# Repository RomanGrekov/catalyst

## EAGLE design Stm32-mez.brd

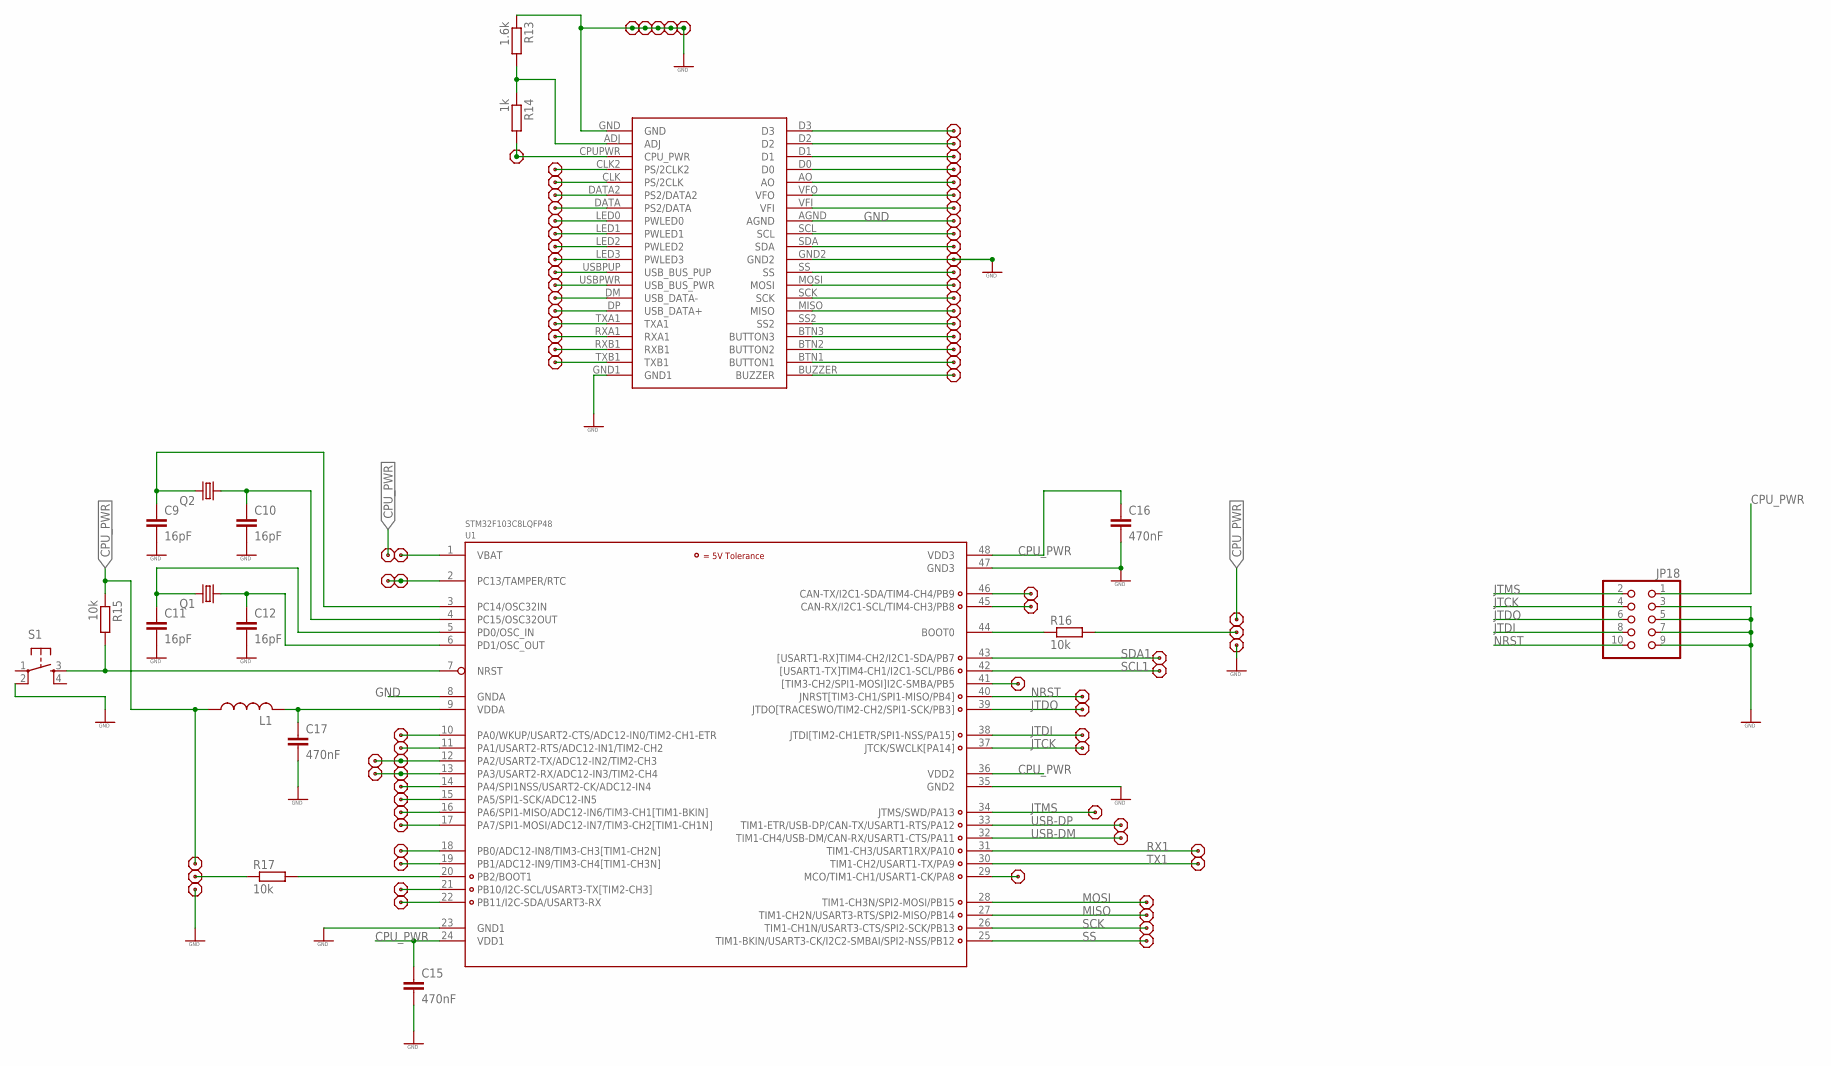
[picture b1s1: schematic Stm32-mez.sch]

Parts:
C9, C10, C11, C12: 16pF; C1206
C15, C16, C17: 470nF; C1206
JP5, JP6, JP7, JP8, JP10, JP11, JP12, JP13, JP14, JP15, JP16, JP17, JP19, JP20, JP21, JP22, JP23, JP24, JP25, JP26, JP27, JP28, JP29, JP30, JP31, JP32, JP33, JP34, JP35, JP36, JP37, JP38, JP39, JP40, JP41, JP42, JP43, JP44, JP45, JP46, JP47, JP48, JP49, JP50, JP51, JP52, JP53, JP54, JP55, JP56, JP57, JP58, JP59, JP60, JP61, JP62, JP63, JP64, JP65, JP66, JP67, JP68, JP69, JP70, JP71, JP72, JP73, JP74, JP75, JP76, JP77, JP78, JP79, JP80, JP81, JP82, JP83, JP84, JP85, JP86, JP87, JP88, JP89, JP90, JP91: PINHD-1X1PIN; 1X01
JP18: PINHD-2X5; 2X05
L1: L-US0207/15; 0207/15
Q1: CRYSTALHC49U-V; HC49U-V
Q2: CRYSTALTC26H; TC26H
R13: 1.6k; R1206
R14: 1k; R1206
R15, R16, R17: 10k; R1206
S1: TAC_SWITCHPTH; TACTILE-PTH
U1: STM32F103C8LQFP48; LQFP48
U$2: CPU_CON; CPU_SHIELD

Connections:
CPU_PWR: C15.1, C16.1, JP5.1, JP16.1, JP18.1, JP24.1, JP54.1, L1.1, R14.2, R15.1, U1.24 (VDD1), U1.36 (VDD2), U1.48 (VDD3), U$2.CPUPWR (CPU_PWR)
GND: C9.2, C10.2, C11.2, C12.2, C15.2, C16.2, C17.2, JP10.1, JP11.1, JP12.1, JP13.1, JP14.1, JP18.3, JP18.5, JP18.7, JP18.9, JP25.1, JP55.1, JP90.1, JP91.1, R13.1, S1.2, U1.8 (GNDA), U1.23 (GND1), U1.35 (GND2), U1.47 (GND3), U$2.AGND, U$2.GND, U$2.GND1, U$2.GND2
JTCK: JP18.4, JP22.1, U1.37 (JTCK/SWCLK[PA14])
JTDI: JP18.8, JP21.1, U1.38 (JTDI[TIM2-CH1ETR/SPI1-NSS/PA15])
JTDO: JP18.6, JP20.1, U1.39 (JTDO[TRACESWO/TIM2-CH2/SPI1-SCK/PB3])
JTMS: JP18.2, JP26.1, U1.34 (JTMS/SWD/PA13)
MISO: JP32.1, U1.27 (TIM1-CH2N/USART3-RTS/SPI2-MISO/PB14)
MOSI: JP31.1, U1.28 (TIM1-CH3N/SPI2-MOSI/PB15)
unnamed: R15.2, S1.3, U1.7 (NRST)
unnamed: R13.2, R14.1, U$2.ADJ
unnamed: C12.1, Q1.1, U1.6 (PD1/OSC_OUT)
unnamed: C11.1, Q1.2, U1.5 (PD0/OSC_IN)
unnamed: C10.1, Q2.1, U1.4 (PC15/OSC32OUT)
unnamed: C9.1, Q2.2, U1.3 (PC14/OSC32IN)
unnamed: JP8.1, JP17.1, U1.2 (PC13/TAMPER/RTC)
unnamed: R16.1, U1.44 (BOOT0)
unnamed: JP23.1, R16.2
unnamed: JP38.1, U1.46 (CAN-TX/I2C1-SDA/TIM4-CH4/PB9)
unnamed: JP37.1, U1.45 (CAN-RX/I2C1-SCL/TIM4-CH3/PB8)
unnamed: JP39.1, U1.41 ([TIM3-CH2/SPI1-MOSI]I2C-SMBA/PB5)
unnamed: JP40.1, U1.29 (MCO/TIM1-CH1/USART1-CK/PA8)
unnamed: JP41.1, U1.10 (PA0/WKUP/USART2-CTS/ADC12-IN0/TIM2-CH1-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)
unnamed: JP43.1, U1.11 (PA1/USART2-RTS/ADC12-IN1/TIM2-CH2)
unnamed: JP6.1, JP42.1, U1.12 (PA2/USART2-TX/ADC12-IN2/TIM2-CH3)
unnamed: JP7.1, JP44.1, U1.13 (PA3/USART2-RX/ADC12-IN3/TIM2-CH4)
unnamed: JP45.1, U1.14 (PA4/SPI1NSS/USART2-CK/ADC12-IN4)
unnamed: JP46.1, U1.15 (PA5/SPI1-SCK/ADC12-IN5)
unnamed: JP47.1, U1.16 (PA6/SPI1-MISO/ADC12-IN6/TIM3-CH1[TIM1-B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)
unnamed: JP48.1, U1.17 (PA7/SPI1-MOSI/ADC12-IN7/TIM3-CH2[TIM1-C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)
unnamed: JP49.1, U1.18 (PB0/ADC12-IN8/TIM3-CH3[TIM1-CH2N])
unnamed: JP50.1, U1.19 (PB1/ADC12-IN9/TIM3-CH4[TIM1-CH3N])
unnamed: R17.2, U1.20 (PB2/BOOT1)
unnamed: JP52.1, U1.21 (PB10/I2C-SCL/USART3-TX[TIM2-CH3])
unnamed: JP53.1, U1.22 (PB11/I2C-SDA/USART3-RX)
unnamed: JP51.1, R17.1
unnamed: JP73.1, U$2.D3
unnamed: JP72.1, U$2.D2
unnamed: JP71.1, U$2.D1
unnamed: JP70.1, U$2.D0
unnamed: JP69.1, U$2.AO
unnamed: JP68.1, U$2.VFO
unnamed: JP67.1, U$2.VFI
unnamed: JP66.1, U$2.SCL
unnamed: JP65.1, U$2.SDA
unnamed: JP64.1, U$2.SS
unnamed: JP63.1, U$2.MOSI
unnamed: JP62.1, U$2.SCK
unnamed: JP61.1, U$2.MISO
unnamed: JP60.1, U$2.SS2
unnamed: JP59.1, U$2.BTN3 (BUTTON3)
unnamed: JP58.1, U$2.BTN2 (BUTTON2)
unnamed: JP57.1, U$2.BTN1 (BUTTON1)
unnamed: JP56.1, U$2.BUZZER
unnamed: JP74.1, U$2.TXB1
unnamed: JP75.1, U$2.RXB1
unnamed: JP76.1, U$2.RXA1
unnamed: JP77.1, U$2.TXA1
unnamed: JP78.1, U$2.DP (USB_DATA+)
unnamed: JP79.1, U$2.DM (USB_DATA-)
unnamed: JP80.1, U$2.USBPWR (USB_BUS_PWR)
unnamed: JP81.1, U$2.USBPUP (USB_BUS_PUP)
unnamed: JP82.1, U$2.LED3 (PWLED3)
unnamed: JP83.1, U$2.LED2 (PWLED2)
unnamed: JP84.1, U$2.LED1 (PWLED1)
unnamed: JP85.1, U$2.LED0 (PWLED0)
unnamed: JP86.1, U$2.DATA (PS2/DATA)
unnamed: JP87.1, U$2.DATA2 (PS2/DATA2)
unnamed: JP88.1, U$2.CLK (PS/2CLK)
unnamed: JP89.1, U$2.CLK2 (PS/2CLK2)
NRST: JP18.10, JP19.1, U1.40 (JNRST[TIM3-CH1/SPI1-MISO/PB4])
RX1: JP27.1, U1.31 (TIM1-CH3/USART1RX/PA10)
SCK: JP33.1, U1.26 (TIM1-CH1N/USART3-CTS/SPI2-SCK/PB13)
SCL1: JP36.1, U1.42 ([USART1-TX]TIM4-CH1/I2C1-SCL/PB6)
SDA1: JP35.1, U1.43 ([USART1-RX]TIM4-CH2/I2C1-SDA/PB7)
SS: JP34.1, U1.25 (TIM1-BKIN/USART3-CK/I2C2-SMBAI/SPI2-NSS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)
TX1: JP28.1, U1.30 (TIM1-CH2/USART1-TX/PA9)
USB-DM: JP29.1, U1.32 (TIM1-CH4/USB-DM/CAN-RX/USART1-CTS/PA11)
USB-DP: JP30.1, U1.33 (TIM1-ETR/USB-DP/CAN-TX/USART1-RTS/PA12)
VBAT: JP15.1, U1.1 (VBAT)
VDDA: C17.1, L1.2, U1.9 (VDDA)

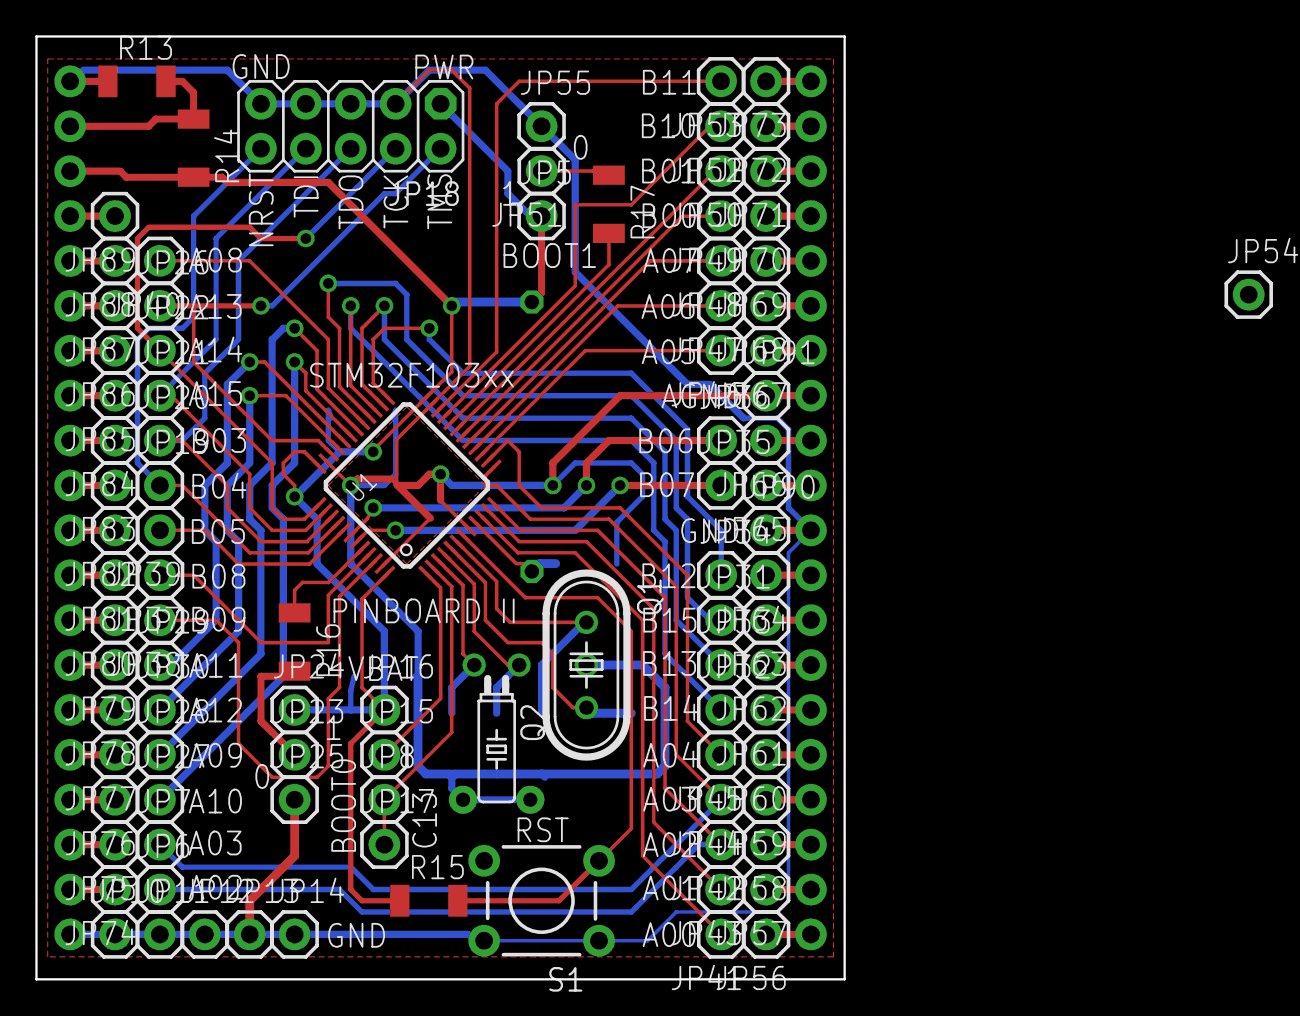
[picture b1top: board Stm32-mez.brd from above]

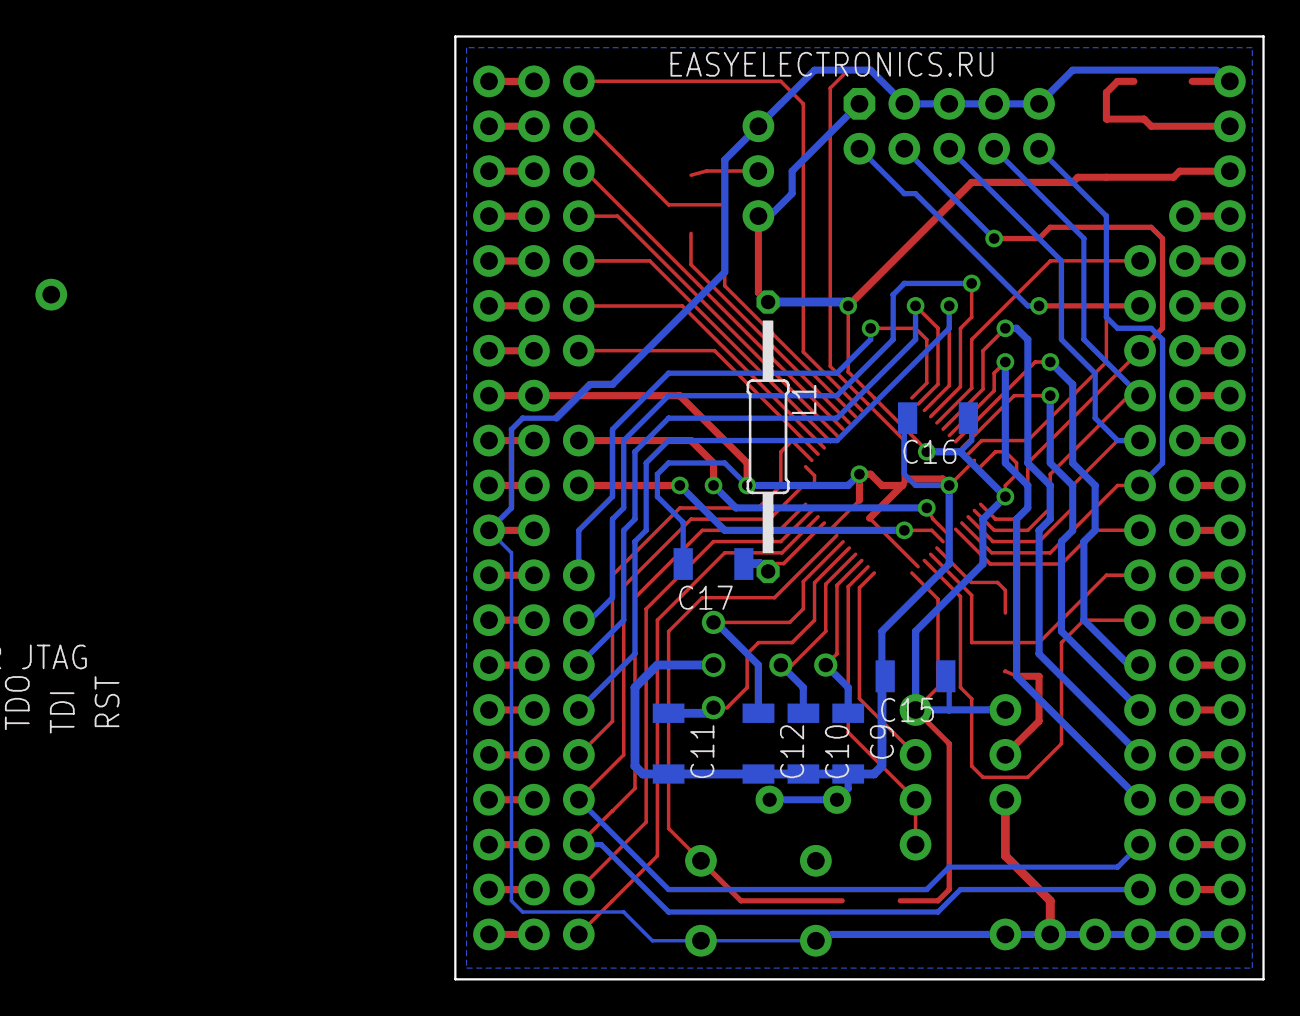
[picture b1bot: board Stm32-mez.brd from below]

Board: 2 copper layers, 45.7 x 53.3 mm, 104 parts (8 on the bottom side), 80 nets.

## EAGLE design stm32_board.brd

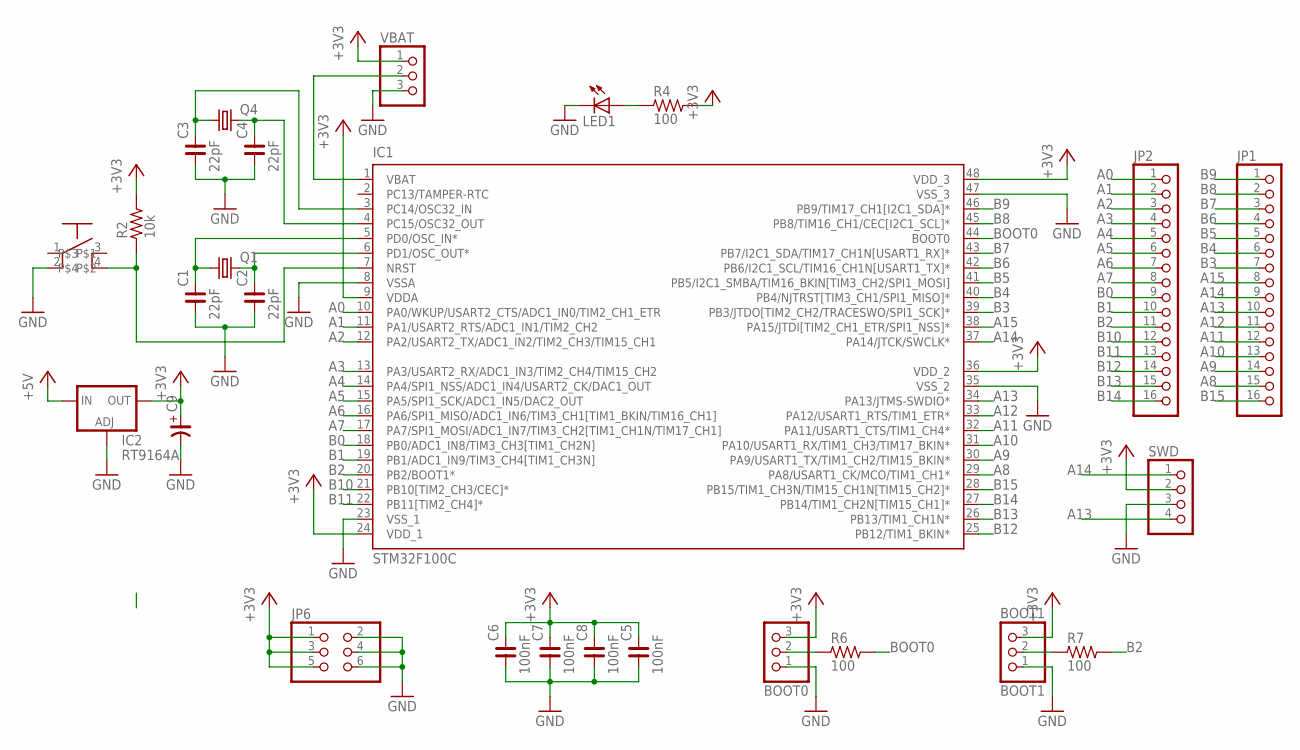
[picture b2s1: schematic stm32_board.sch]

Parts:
BOOT0: PINHD-1X3; 1X03
BOOT1: BOOT1; 1X03
C1, C2, C3, C4: 22pF; C1206
C5, C6, C7, C8: 100nF; C1206
C9: CP_SV-D; CSV-D
IC1: STM32F100C; LQFP48
IC2: RT9164A; DPACK
JP1, JP2: PINHD-1X16; 1X16
JP6: PINHD-2X3; 2X03
LED1: LEDCHIPLED_0805; CHIPLED_0805
Q1: CRYSTALHC49U-V; HC49U-V
Q4: CRYSTALTC26V; TC26V
R2: 10k; R1206
R4, R6, R7: 100; R1206
S1: BUTTON
SWD: PINHD-1X4; 1X04
VBAT: PINHD-1X3; 1X03

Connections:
+3V3: BOOT0.3, BOOT1.3, C5.2, C6.2, C7.2, C8.2, C9.+, IC1.9 (VDDA), IC1.24 (VDD_1), IC1.36 (VDD_2), IC1.48 (VDD_3), IC2.4 (OUT), JP6.1, JP6.3, JP6.5, R2.2, R4.2, SWD.2, VBAT.1
+5V: IC2.3 (IN)
A0: IC1.10 (PA0/WKUP/USART2_CTS/ADC1_IN0/TIM2_CH1_E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), JP2.1
A1: IC1.11 (PA1/USART2_RTS/ADC1_IN1/TIM2_CH2), JP2.2
A2: IC1.12 (PA2/USART2_TX/ADC1_IN2/TIM2_CH3/TIM15_C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), JP2.3
A3: IC1.13 (PA3/USART2_RX/ADC1_IN3/TIM2_CH4/TIM15_C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), JP2.4
A4: IC1.14 (PA4/SPI1_NSS/ADC1_IN4/USART2_CK/DAC1_OUT), JP2.5
A5: IC1.15 (PA5/SPI1_SCK/ADC1_IN5/DAC2_OUT), JP2.6
A6: IC1.16 (PA6/SPI1_MISO/ADC1_IN6/TIM3_CH1[TIM1_BK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), JP2.7
A7: IC1.17 (PA7/SPI1_MOSI/ADC1_IN7/TIM3_CH2[TIM1_CH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), JP2.8
A8: IC1.29 (PA8/USART1_CK/MCO/TIM1_CH1*), JP1.15
A9: IC1.30 (PA9/USART1_TX/TIM1_CH2/TIM15_BKIN*), JP1.14
A10: IC1.31 (PA10/USART1_RX/TIM1_CH3/TIM17_BKIN*), JP1.13
A11: IC1.32 (PA11/USART1_CTS/TIM1_CH4*), JP1.12
A12: IC1.33 (PA12/USART1_RTS/TIM1_ETR*), JP1.11
A13: IC1.34 (PA13/JTMS-SWDIO*), JP1.10, SWD.4
A14: IC1.37 (PA14/JTCK/SWCLK*), JP1.9, SWD.1
A15: IC1.38 (PA15/JTDI[TIM2_CH1_ETR/SPI1_NSS]*), JP1.8
B0: IC1.18 (PB0/ADC1_IN8/TIM3_CH3[TIM1_CH2N]), JP2.9
B1: IC1.19 (PB1/ADC1_IN9/TIM3_CH4[TIM1_CH3N]), JP2.10
B2: IC1.20 (PB2/BOOT1*), JP2.11, R7.2
B3: IC1.39 (PB3/JTDO[TIM2_CH2/TRACESWO/SPI1_SCK]*), JP1.7
B4: IC1.40 (PB4/NJTRST[TIM3_CH1/SPI1_MISO]*), JP1.6
B5: IC1.41 (PB5/I2C1_SMBA/TIM16_BKIN[TIM3_CH2/SPI1_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), JP1.5
B6: IC1.42 (PB6/I2C1_SCL/TIM16_CH1N[USART1_TX]*), JP1.4
B7: IC1.43 (PB7/I2C1_SDA/TIM17_CH1N[USART1_RX]*), JP1.3
B8: IC1.45 (PB8/TIM16_CH1/CEC[I2C1_SCL]*), JP1.2
B9: IC1.46 (PB9/TIM17_CH1[I2C1_SDA]*), JP1.1
B10: IC1.21 (PB10[TIM2_CH3/CEC]*), JP2.12
B11: IC1.22 (PB11[TIM2_CH4]*), JP2.13
B12: IC1.25 (PB12/TIM1_BKIN*), JP2.14
B13: IC1.26 (PB13/TIM1_CH1N*), JP2.15
B14: IC1.27 (PB14/TIM1_CH2N[TIM15_CH1]*), JP2.16
B15: IC1.28 (PB15/TIM1_CH3N/TIM15_CH1N[TIM15_CH2]*), JP1.16
BOOT0: IC1.44 (BOOT0), R6.2
GND: BOOT0.1, BOOT1.1, C1.1, C2.1, C3.1, C4.1, C5.1, C6.1, C7.1, C8.1, C9.-, IC1.8 (VSSA), IC1.23 (VSS_1), IC1.35 (VSS_2), IC1.47 (VSS_3), IC2.1 (ADJ), JP6.2, JP6.4, JP6.6, LED1.C, S1.2, SWD.3, VBAT.3
unnamed: C1.2, IC1.5 (PD0/OSC_IN*), Q1.1
unnamed: C2.2, IC1.6 (PD1/OSC_OUT*), Q1.2
unnamed: IC1.1 (VBAT), VBAT.2
unnamed: BOOT0.2, R6.1
unnamed: BOOT1.2, R7.1
unnamed: IC1.7 (NRST), R2.1, S1.4
unnamed: LED1.A, R4.1
unnamed: C3.2, IC1.3 (PC14/OSC32_IN), Q4.1
unnamed: C4.2, IC1.4 (PC15/OSC32_OUT), Q4.2

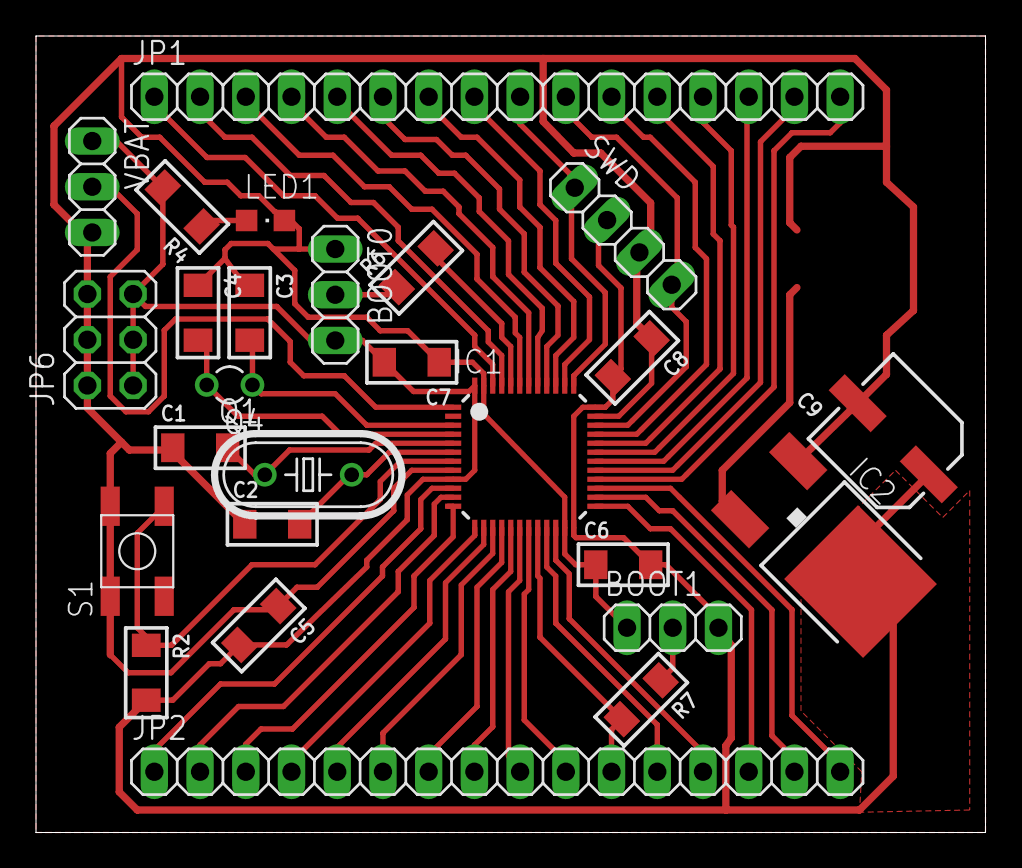
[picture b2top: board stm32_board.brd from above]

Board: 2 copper layers, 52.8 x 44.2 mm, 26 parts (0 on the bottom side), 44 nets.

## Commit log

2015-01-11 Added board for stm32controller
